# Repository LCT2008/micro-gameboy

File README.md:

# Micro Gameboy

A pocket-size gaming console powered by the **ATtiny412**, featured with the classic **Flappy Bird** game.

Designed around a compact custom PCB, Micro Gameboy features a monochrome I²C OLED display, two physical control buttons, and a simple battery-powered architecture using two AAA batteries.

More than just a miniature gaming console, it is designed to support compatible custom games that can be flashed directly through its **UPDI programming port**.

---

## Features

- **ATtiny412 Microcontroller** — Compact AVR microcontroller powering the console.
- **OLED Display** — Monochrome I²C display for game graphics and interface.
- **Two-Button Control** — Simple physical controls for gameplay.
- **AAA Battery Powered** — Operates using two standard AAA batteries.
- **UPDI Programming** — Flash compatible custom games through the UPDI interface.
- **Custom PCB** — Designed and developed using KiCad.

## Hardware

| Component       | Description         |
| --------------- | ------------------- |
| Microcontroller | ATtiny412           |
| Display         | I²C Monochrome OLED |
| Input           | 2× Push Buttons     |
| Power           | 2× AAA Batteries    |
| Programming     | UPDI                |

## Gallery

### Schematics

### PCB Design

## Firmware & Games

Micro Gameboy comes preloaded with a recreation of the classic **Flappy Bird** game.

The ATtiny412's UPDI programming interface also allows compatible firmware and games to be flashed onto the microcontroller, opening the possibility for additional games and custom applications.

*Game compatibility depends on the available hardware resources, display interface, and firmware implementation.*

## PCB Design

The custom schematic and PCB layout are developed using **KiCad**.

Project design files and development documentation are maintained in this repository.

## Development Journal

Follow the project's engineering progress, design decisions, technical challenges, and development milestones in [`JOURNAL.md`](JOURNAL.md).

---
**Designed with love ❤️ by LCT2008**

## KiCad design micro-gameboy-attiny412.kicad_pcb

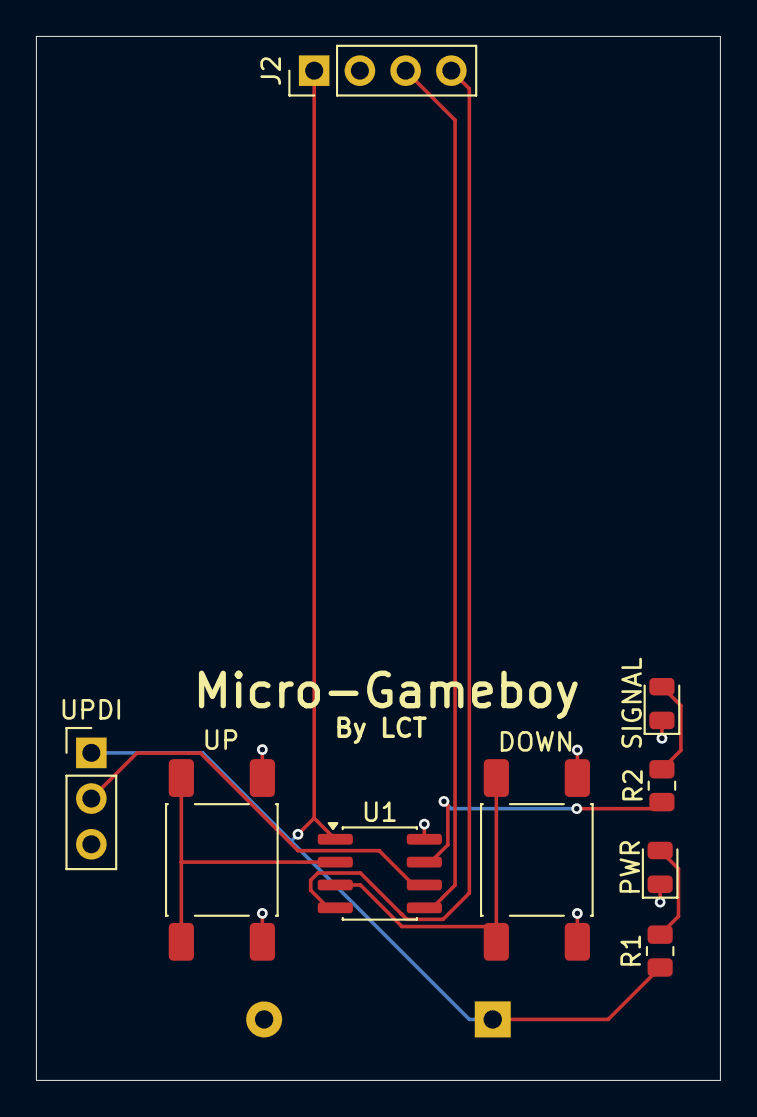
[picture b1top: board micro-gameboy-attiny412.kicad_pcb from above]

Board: 2 copper layers, 38.0 x 58.0 mm, 10 parts (1 on the bottom side), 10 nets.

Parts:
BT1: Battery_Cell; BatteryHolder_Keystone_2468_2xAAA
DOWN: SW_Push; SW_Push_1P1T_NO_E-Switch_TL3301NxxxxxG
J2: SH1106_OLED_1.3_I2C; PinHeader_1x04_P2.54mm_Vertical
PWR: LED; LED_0805_2012Metric
R1, R2: 68R; R_0805_2012Metric
SIGNAL: LED; LED_0805_2012Metric
U1: ATtiny412-SS; SOIC-8_3.9x4.9mm_P1.27mm
UP: SW_Push; SW_Push_1P1T_NO_E-Switch_TL3301NxxxxxG
UPDI: Conn_01x03_Pin; PinHeader_1x03_P2.54mm_Vertical

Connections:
GND: BT1.2 (-), DOWN.1, J2.2, PWR.1 (K), SIGNAL.1 (K), U1.8 (GND), UP.1, UPDI.3
unnamed: PWR.2 (A), R1.1
unnamed: R2.1, SIGNAL.2 (A)
PA1: J2.4, U1.4 (PA1)
PA2: J2.3, U1.5 (PA2)
PA3: R2.2, U1.7 (PA3)
PA6: U1.2 (PA6), UP.2
PA7: DOWN.2, U1.3 (PA7)
VCC: BT1.1 (+), J2.1, R1.2, U1.1 (VCC), UPDI.1
~RESET/PA0: U1.6 (~RESET/PA0), UPDI.2
